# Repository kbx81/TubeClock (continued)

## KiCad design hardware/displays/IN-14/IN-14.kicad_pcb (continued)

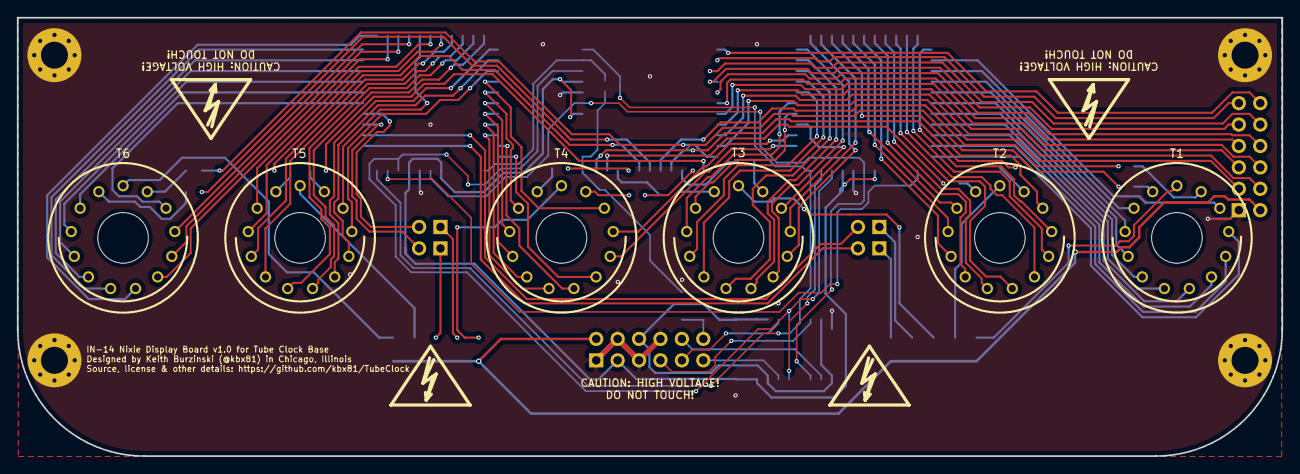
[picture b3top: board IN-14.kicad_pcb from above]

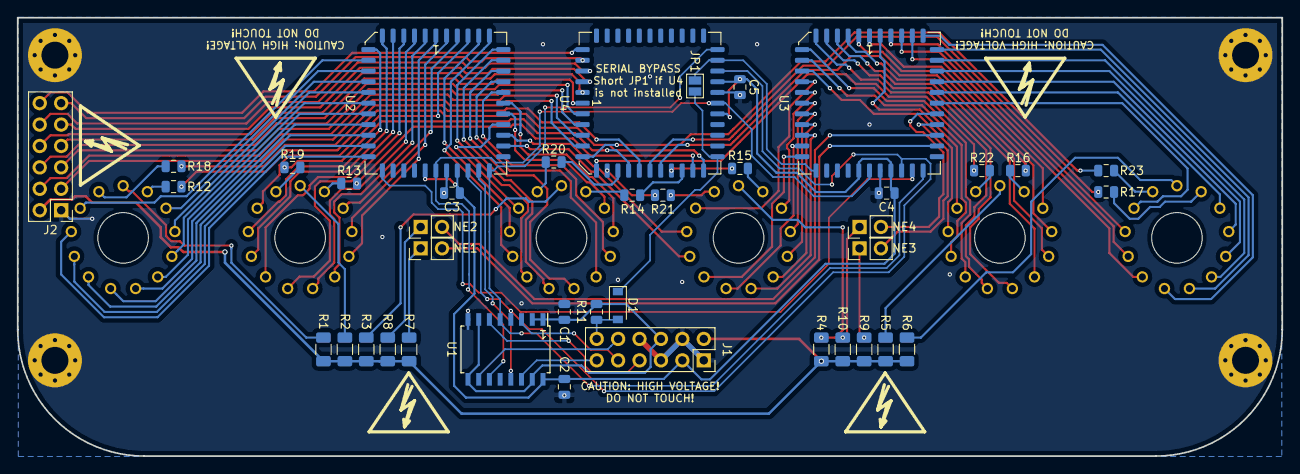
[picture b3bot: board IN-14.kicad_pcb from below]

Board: 2 copper layers, 150.0 x 52.0 mm, 50 parts (40 on the bottom side), 124 nets.

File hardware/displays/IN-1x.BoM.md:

# Nixie Tube Display Board Bill of Materials (BoM)

## Parts

|Reference                                           |Quantity|Value                    |Footprint                                                 |
|----------------------------------------------------|--------|-------------------------|----------------------------------------------------------|
|C2 C1 C3 C4 C5                                      |5       |100 nF, 16 V             |Capacitor_SMD:C_0805_2012Metric                           |
|D1                                                  |1       |1N4148                   |Diode_SMD:D_SOD-123                                       |
|J1                                                  |1       |Conn_02x06_Odd_Even      |Connector_PinSocket_2.54mm:PinSocket_2x06_P2.54mm_Vertical|
|J2                                                  |1       |Conn_02x06_Odd_Even      |Connector_PinHeader_2.54mm:PinHeader_2x06_P2.54mm_Vertical|
|NE4 NE3 NE1 NE2                                     |4       |Lamp_Neon                |Connector_PinHeader_2.54mm:PinHeader_1x02_P2.54mm_Vertical|
|R10 R9 R8 R7                                        |4       |470K                     |Resistor_SMD:R_1206_3216Metric                            |
|R11 R12 R13 R14 R15 R16 R17 R18 R19 R20 R21 R22 R23 |13      |10K                      |Resistor_SMD:R_0805_2012Metric                            |
|R6 R3 R5 R4 R2 R1                                   |6       |10K (2K2 for IN-18) .25 W|Resistor_SMD:R_1206_3216Metric                            |
|T1 T2 T3 T4 T5 T6                                   |6       |IN-1x_Nixie_Tube         |TubeClock:Nixie_IN-1x                                     |
|U1                                                  |1       |CD40109B                 |Package_SO:SOIC-16W_5.3x10.2mm_P1.27mm                    |
|U2 U3 U4*                                           |3       |HV5622                   |Package_LCC:PLCC-44_16.6x16.6mm_P1.27mm                   |

## Additional parts you may need

For IN-12 and IN-18 boards, machine pin sockets are highly recommended -- **do not** solder the tubes into the boards! `Mill-Max` part number `0327-0-15-01-34-27-10-0` is a perfect fit for these tubes!

For the seperator/colon indicator lamps (NE1 through NE4), any "A1B" neon indicator lamp should suffice. I used `VCC` part number `A1B`. Some `INS-1` tubes should also work well, particularly on the IN-12 boards.

## IMPORTANT!

**Pay extra super close attention to the polarity of D1!** Bad things will happen if it is installed backwards. :(

### Notes

For IN-12 and IN-18 tubes, use machine pin sockets suggested above. Since IN-14 and IN-16 tubes have wire leads, they should be soldered directly into the boards.

*U4 is not present on IN-18 display boards. On the other boards, it is not required if you don't care about the lovely decimal points in the smaller tubes. :) **Bridge the solder jumper if U4 is *not* installed** on these boards.

R12 through R23 are additional series resistors for tube decimal points. They are not present on IN-18 boards and are otherwise not necessary if decimal points will not be used.

## Are you shopping?

I've created an [Octopart](https://www.octopart.com) BoM [here](https://octopart.com/bom-tool/LsrgprMy)!

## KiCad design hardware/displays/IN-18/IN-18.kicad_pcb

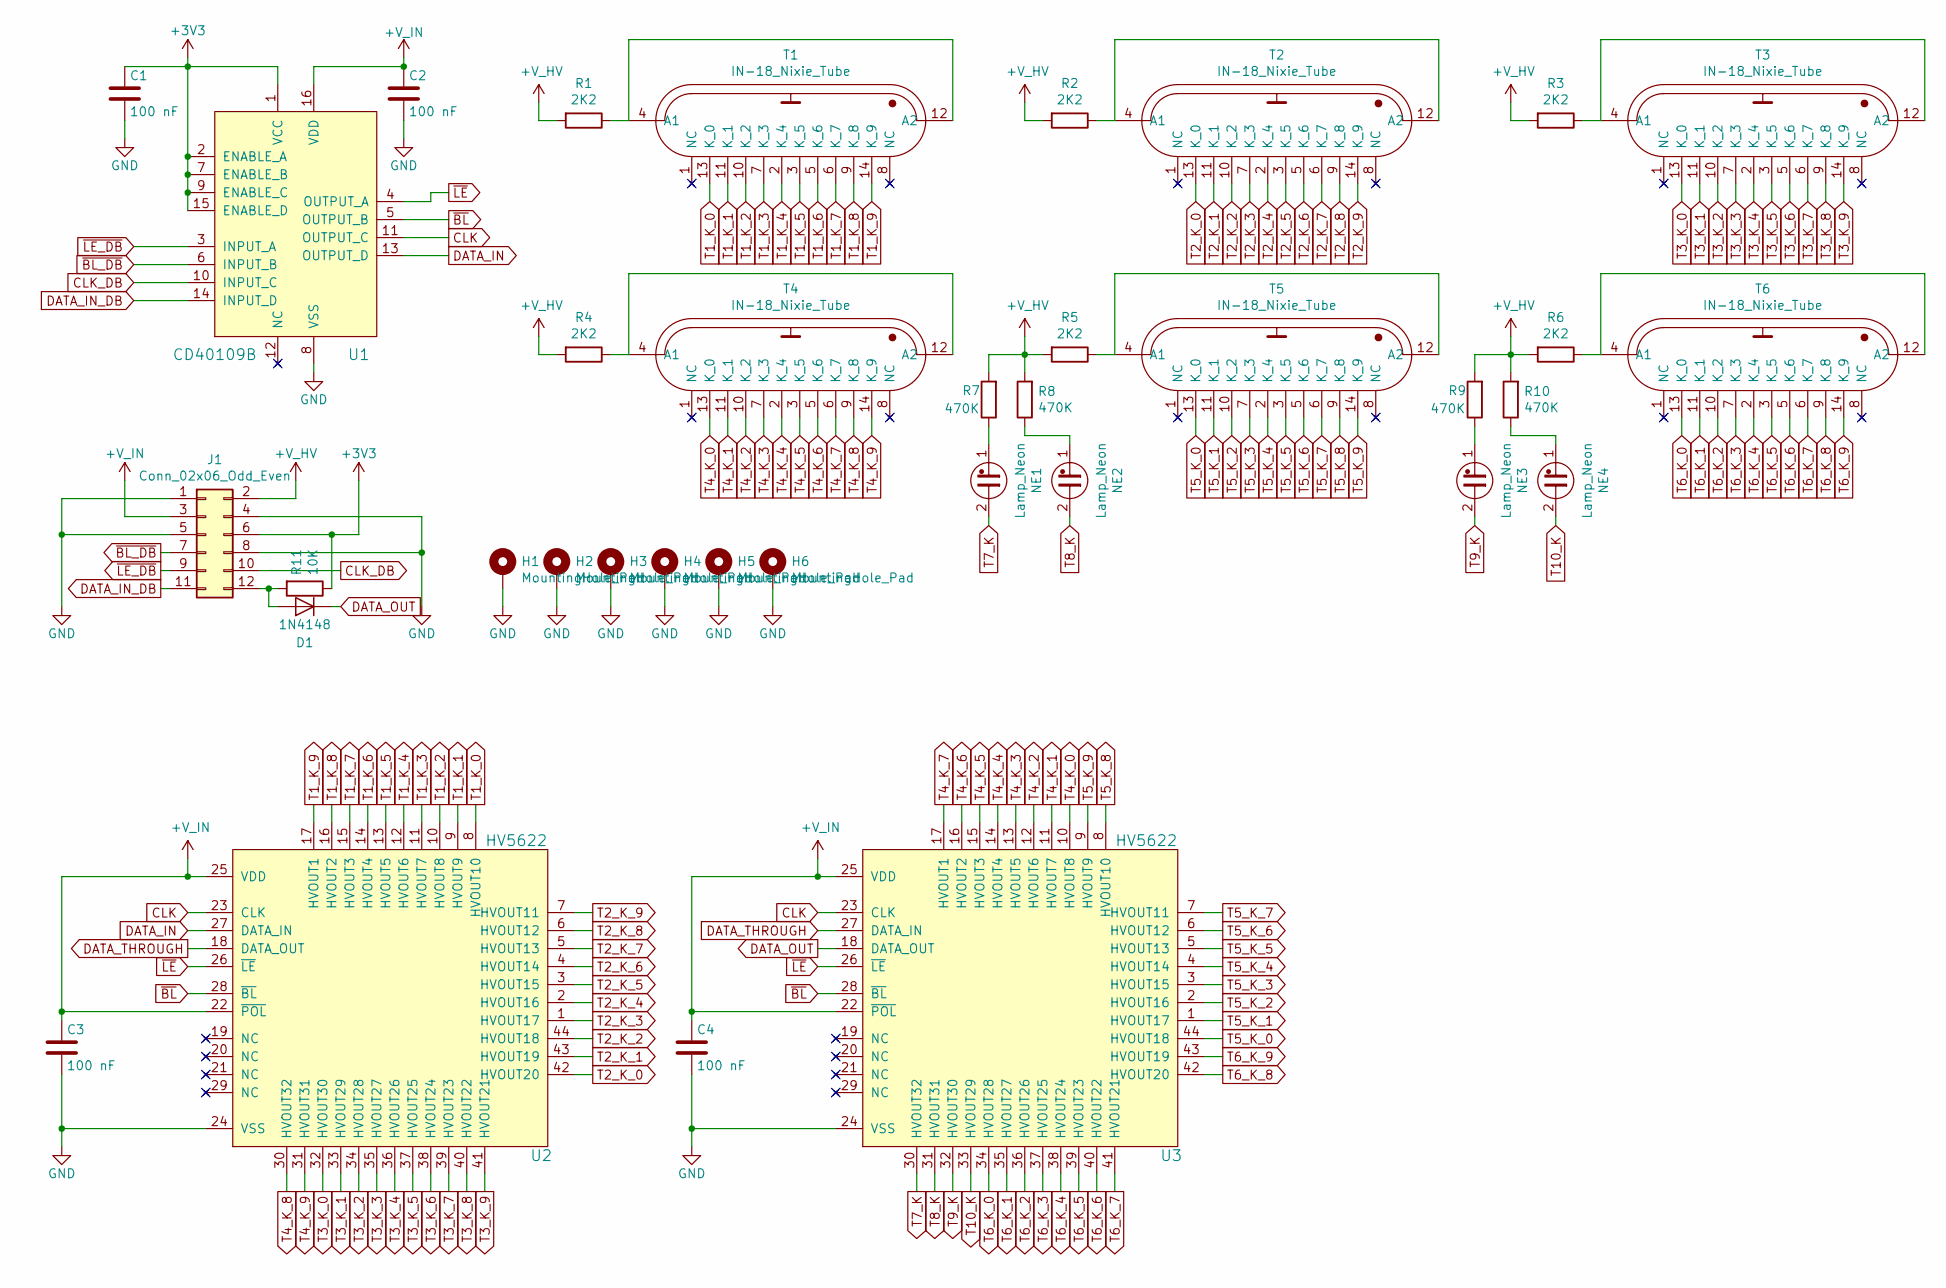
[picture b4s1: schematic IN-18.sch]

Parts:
C1, C2, C3, C4: 100 nF; C_0805_2012Metric
D1: 1N4148; D_SOD-123
H1, H2, H3, H4, H5, H6: MountingHole_Pad; MountingHole_3.2mm_M3_Pad_Via
J1: Conn_02x06_Odd_Even; PinSocket_2x06_P2.54mm_Vertical
NE1, NE2, NE3, NE4: Lamp_Neon; PinSocket_1x02_P2.54mm_Vertical
R1, R2, R3, R4, R5, R6: 2K2; R_1206_3216Metric
R7, R8, R9, R10: 470K; R_1206_3216Metric
R11: 10K; R_0805_2012Metric
T1, T2, T3, T4, T5, T6: IN-18_Nixie_Tube; Nixie_IN-18
U1: CD40109B; SOIC-16W_5.3x10.2mm_P1.27mm
U2, U3: HV5622; PLCC-44_16.6x16.6mm_P1.27mm

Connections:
+3V3: C1.1, J1.6, R11.1, U1.1 (VCC), U1.2 (ENABLE_A), U1.7 (ENABLE_B), U1.9 (ENABLE_C), U1.15 (ENABLE_D)
+V_HV: J1.2, R1.2, R2.2, R3.2, R4.2, R5.2, R6.2, R7.2, R8.2, R9.2, R10.2
+V_IN: C2.1, C3.1, C4.1, J1.3, U1.16 (VDD), U2.22 (~POL~), U2.25 (VDD), U3.22 (~POL~), U3.25 (VDD)
CLK: U1.11 (OUTPUT_C), U2.23 (CLK), U3.23 (CLK)
CLK_DB: J1.10, U1.10 (INPUT_C)
DATA_IN: U1.13 (OUTPUT_D), U2.27 (DATA_IN)
DATA_IN_DB: J1.11, U1.14 (INPUT_D)
DATA_OUT: D1.1 (K), U3.18 (DATA_OUT)
DATA_THROUGH: U2.18 (DATA_OUT), U3.27 (DATA_IN)
GND: C1.2, C2.2, C3.2, C4.2, H1.1, H2.1, H3.1, H4.1, H5.1, H6.1, J1.1, J1.4, J1.5, J1.8, U1.8 (VSS), U2.24 (VSS), U3.24 (VSS)
unnamed: D1.2 (A), J1.12, R11.2
unnamed: NE1.1, R7.1
unnamed: NE2.1, R8.1
unnamed: NE3.1, R9.1
unnamed: NE4.1, R10.1
unnamed: R1.1, T1.4 (A1), T1.12 (A2)
unnamed: R2.1, T2.4 (A1), T2.12 (A2)
unnamed: R3.1, T3.4 (A1), T3.12 (A2)
unnamed: R4.1, T4.4 (A1), T4.12 (A2)
unnamed: R5.1, T5.4 (A1), T5.12 (A2)
unnamed: R6.1, T6.4 (A1), T6.12 (A2)
T1_K_0: T1.13 (K_0), U2.8 (HVOUT10)
T1_K_1: T1.11 (K_1), U2.9 (HVOUT9)
T1_K_2: T1.10 (K_2), U2.10 (HVOUT8)
T1_K_3: T1.7 (K_3), U2.11 (HVOUT7)
T1_K_4: T1.2 (K_4), U2.12 (HVOUT6)
T1_K_5: T1.3 (K_5), U2.13 (HVOUT5)
T1_K_6: T1.5 (K_6), U2.14 (HVOUT4)
T1_K_7: T1.6 (K_7), U2.15 (HVOUT3)
T1_K_8: T1.9 (K_8), U2.16 (HVOUT2)
T1_K_9: T1.14 (K_9), U2.17 (HVOUT1)
T2_K_0: T2.13 (K_0), U2.42 (HVOUT20)
T2_K_1: T2.11 (K_1), U2.43 (HVOUT19)
T2_K_2: T2.10 (K_2), U2.44 (HVOUT18)
T2_K_3: T2.7 (K_3), U2.1 (HVOUT17)
T2_K_4: T2.2 (K_4), U2.2 (HVOUT16)
T2_K_5: T2.3 (K_5), U2.3 (HVOUT15)
T2_K_6: T2.5 (K_6), U2.4 (HVOUT14)
T2_K_7: T2.6 (K_7), U2.5 (HVOUT13)
T2_K_8: T2.9 (K_8), U2.6 (HVOUT12)
T2_K_9: T2.14 (K_9), U2.7 (HVOUT11)
T3_K_0: T3.13 (K_0), U2.32 (HVOUT30)
T3_K_1: T3.11 (K_1), U2.33 (HVOUT29)
T3_K_2: T3.10 (K_2), U2.34 (HVOUT28)
T3_K_3: T3.7 (K_3), U2.35 (HVOUT27)
T3_K_4: T3.2 (K_4), U2.36 (HVOUT26)
T3_K_5: T3.3 (K_5), U2.37 (HVOUT25)
T3_K_6: T3.5 (K_6), U2.38 (HVOUT24)
T3_K_7: T3.6 (K_7), U2.39 (HVOUT23)
T3_K_8: T3.9 (K_8), U2.40 (HVOUT22)
T3_K_9: T3.14 (K_9), U2.41 (HVOUT21)
T4_K_0: T4.13 (K_0), U3.10 (HVOUT8)
T4_K_1: T4.11 (K_1), U3.11 (HVOUT7)
T4_K_2: T4.10 (K_2), U3.12 (HVOUT6)
T4_K_3: T4.7 (K_3), U3.13 (HVOUT5)
T4_K_4: T4.2 (K_4), U3.14 (HVOUT4)
T4_K_5: T4.3 (K_5), U3.15 (HVOUT3)
T4_K_6: T4.5 (K_6), U3.16 (HVOUT2)
T4_K_7: T4.6 (K_7), U3.17 (HVOUT1)
T4_K_8: T4.9 (K_8), U2.30 (HVOUT32)
T4_K_9: T4.14 (K_9), U2.31 (HVOUT31)
T5_K_0: T5.13 (K_0), U3.44 (HVOUT18)
T5_K_1: T5.11 (K_1), U3.1 (HVOUT17)
T5_K_2: T5.10 (K_2), U3.2 (HVOUT16)
T5_K_3: T5.7 (K_3), U3.3 (HVOUT15)
T5_K_4: T5.2 (K_4), U3.4 (HVOUT14)
T5_K_5: T5.3 (K_5), U3.5 (HVOUT13)
T5_K_6: T5.5 (K_6), U3.6 (HVOUT12)
T5_K_7: T5.6 (K_7), U3.7 (HVOUT11)
T5_K_8: T5.9 (K_8), U3.8 (HVOUT10)
T5_K_9: T5.14 (K_9), U3.9 (HVOUT9)
T6_K_0: T6.13 (K_0), U3.34 (HVOUT28)
T6_K_1: T6.11 (K_1), U3.35 (HVOUT27)
T6_K_2: T6.10 (K_2), U3.36 (HVOUT26)
T6_K_3: T6.7 (K_3), U3.37 (HVOUT25)
T6_K_4: T6.2 (K_4), U3.38 (HVOUT24)
T6_K_5: T6.3 (K_5), U3.39 (HVOUT23)
T6_K_6: T6.5 (K_6), U3.40 (HVOUT22)
T6_K_7: T6.6 (K_7), U3.41 (HVOUT21)
T6_K_8: T6.9 (K_8), U3.42 (HVOUT20)
T6_K_9: T6.14 (K_9), U3.43 (HVOUT19)
T7_K: NE1.2, U3.30 (HVOUT32)
T8_K: NE2.2, U3.31 (HVOUT31)
T9_K: NE3.2, U3.32 (HVOUT30)
T10_K: NE4.2, U3.33 (HVOUT29)
~BL_DB~: J1.7, U1.6 (INPUT_B)
~BL~: U1.5 (OUTPUT_B), U2.28 (~BL~), U3.28 (~BL~)
~LE_DB~: J1.9, U1.3 (INPUT_A)
~LE~: U1.4 (OUTPUT_A), U2.26 (~LE~), U3.26 (~LE~)

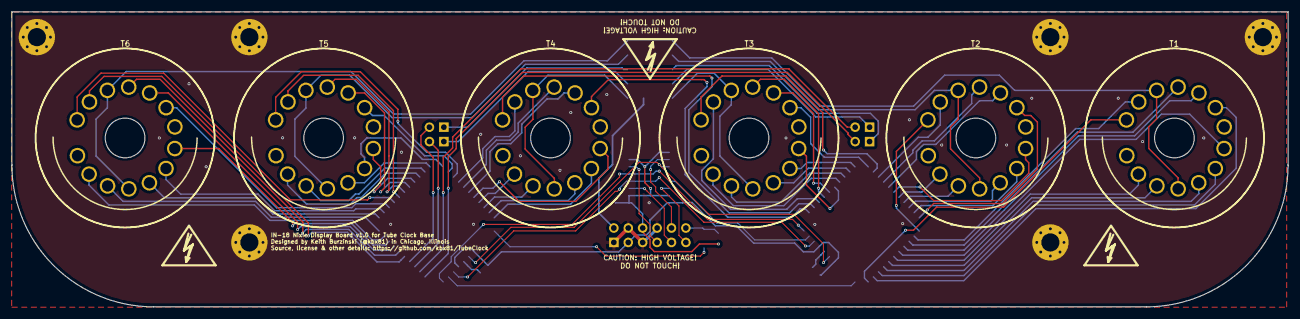
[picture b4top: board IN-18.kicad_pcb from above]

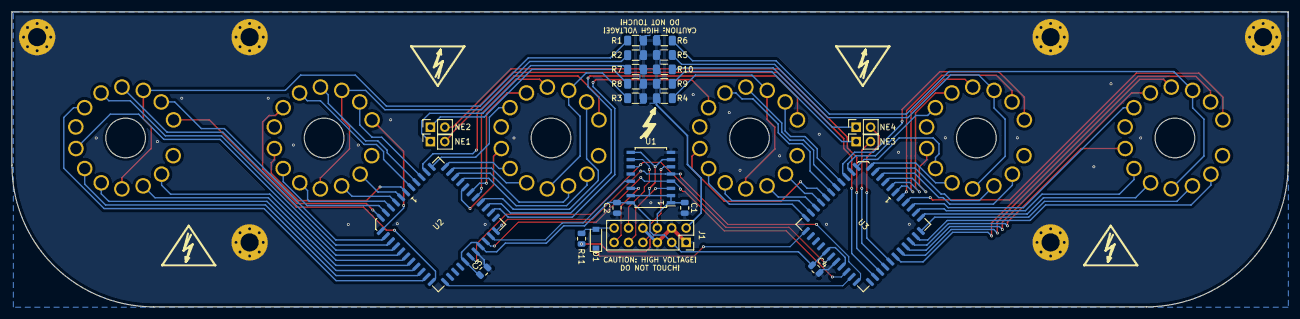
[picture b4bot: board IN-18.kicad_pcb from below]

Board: 2 copper layers, 225.0 x 52.0 mm, 36 parts (24 on the bottom side), 89 nets.

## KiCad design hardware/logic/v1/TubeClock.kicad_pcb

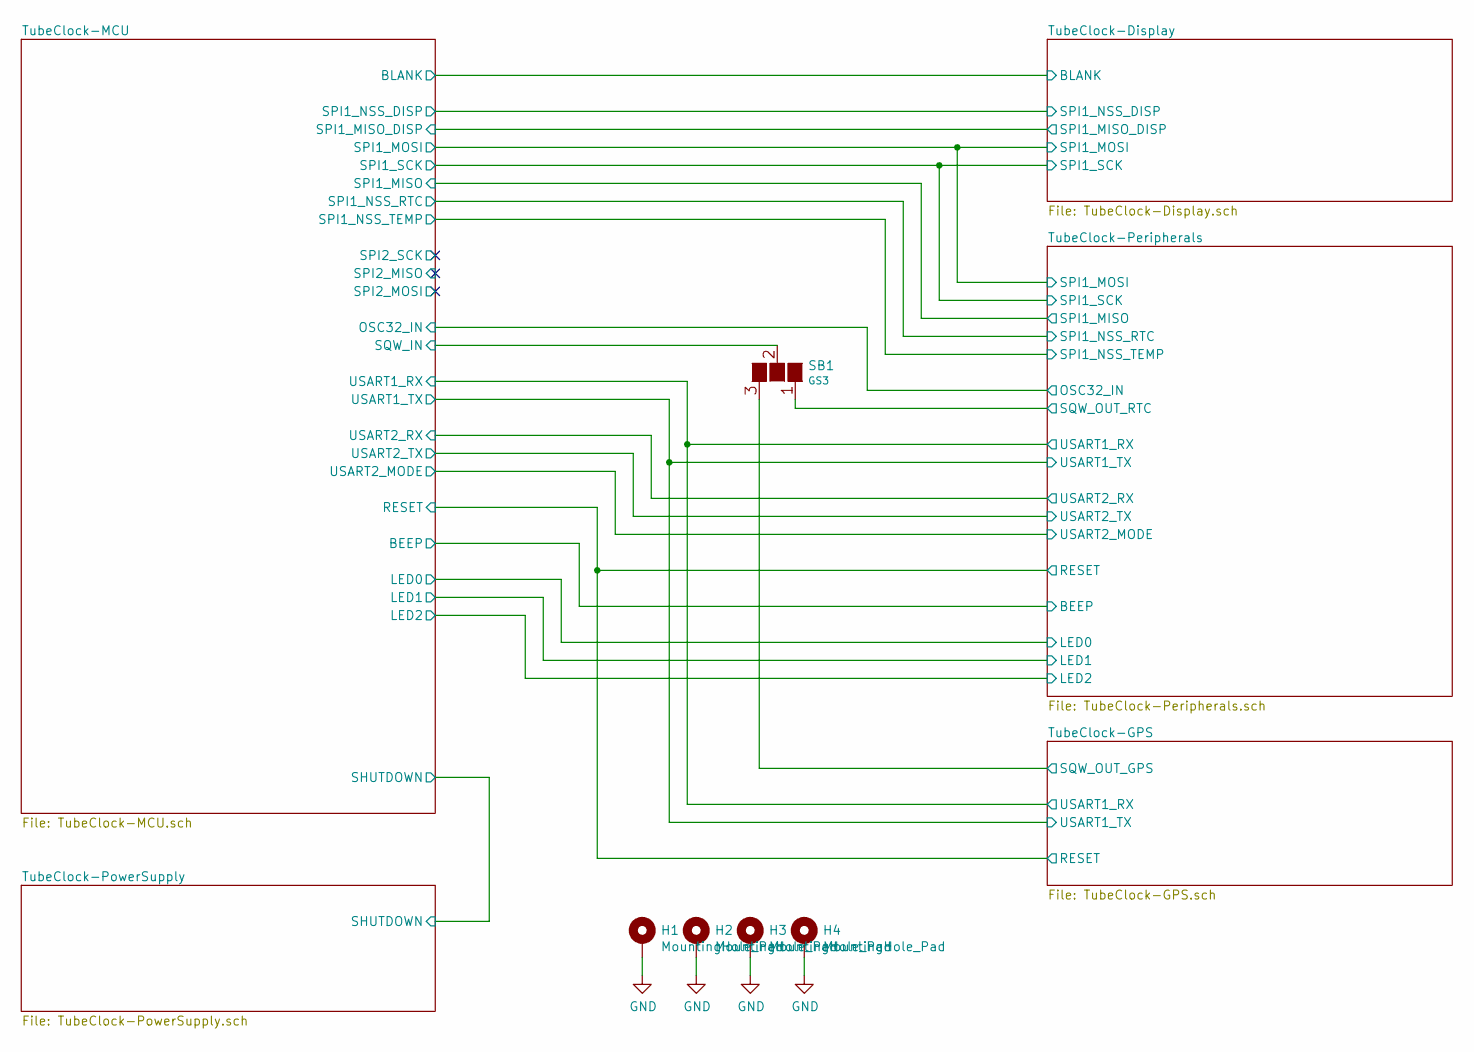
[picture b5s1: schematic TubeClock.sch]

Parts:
H1, H2, H3, H4: MountingHole_Pad; MountingHole_3.2mm_M3_Pad_Via
SB1: GS3; SolderJumper-3_P1.3mm_Open_Pad1.0x1.5mm

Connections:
/TubeClock-GPS/SQW_OUT_GPS: SB1.3 (G3); also elsewhere on the board
/TubeClock-MCU/SQW_IN: SB1.2 (G2); also elsewhere on the board
/TubeClock-Peripherals/SQW_OUT_RTC: SB1.1 (G1); also elsewhere on the board
GND: H1.1, H2.1, H3.1, H4.1; also elsewhere on the board

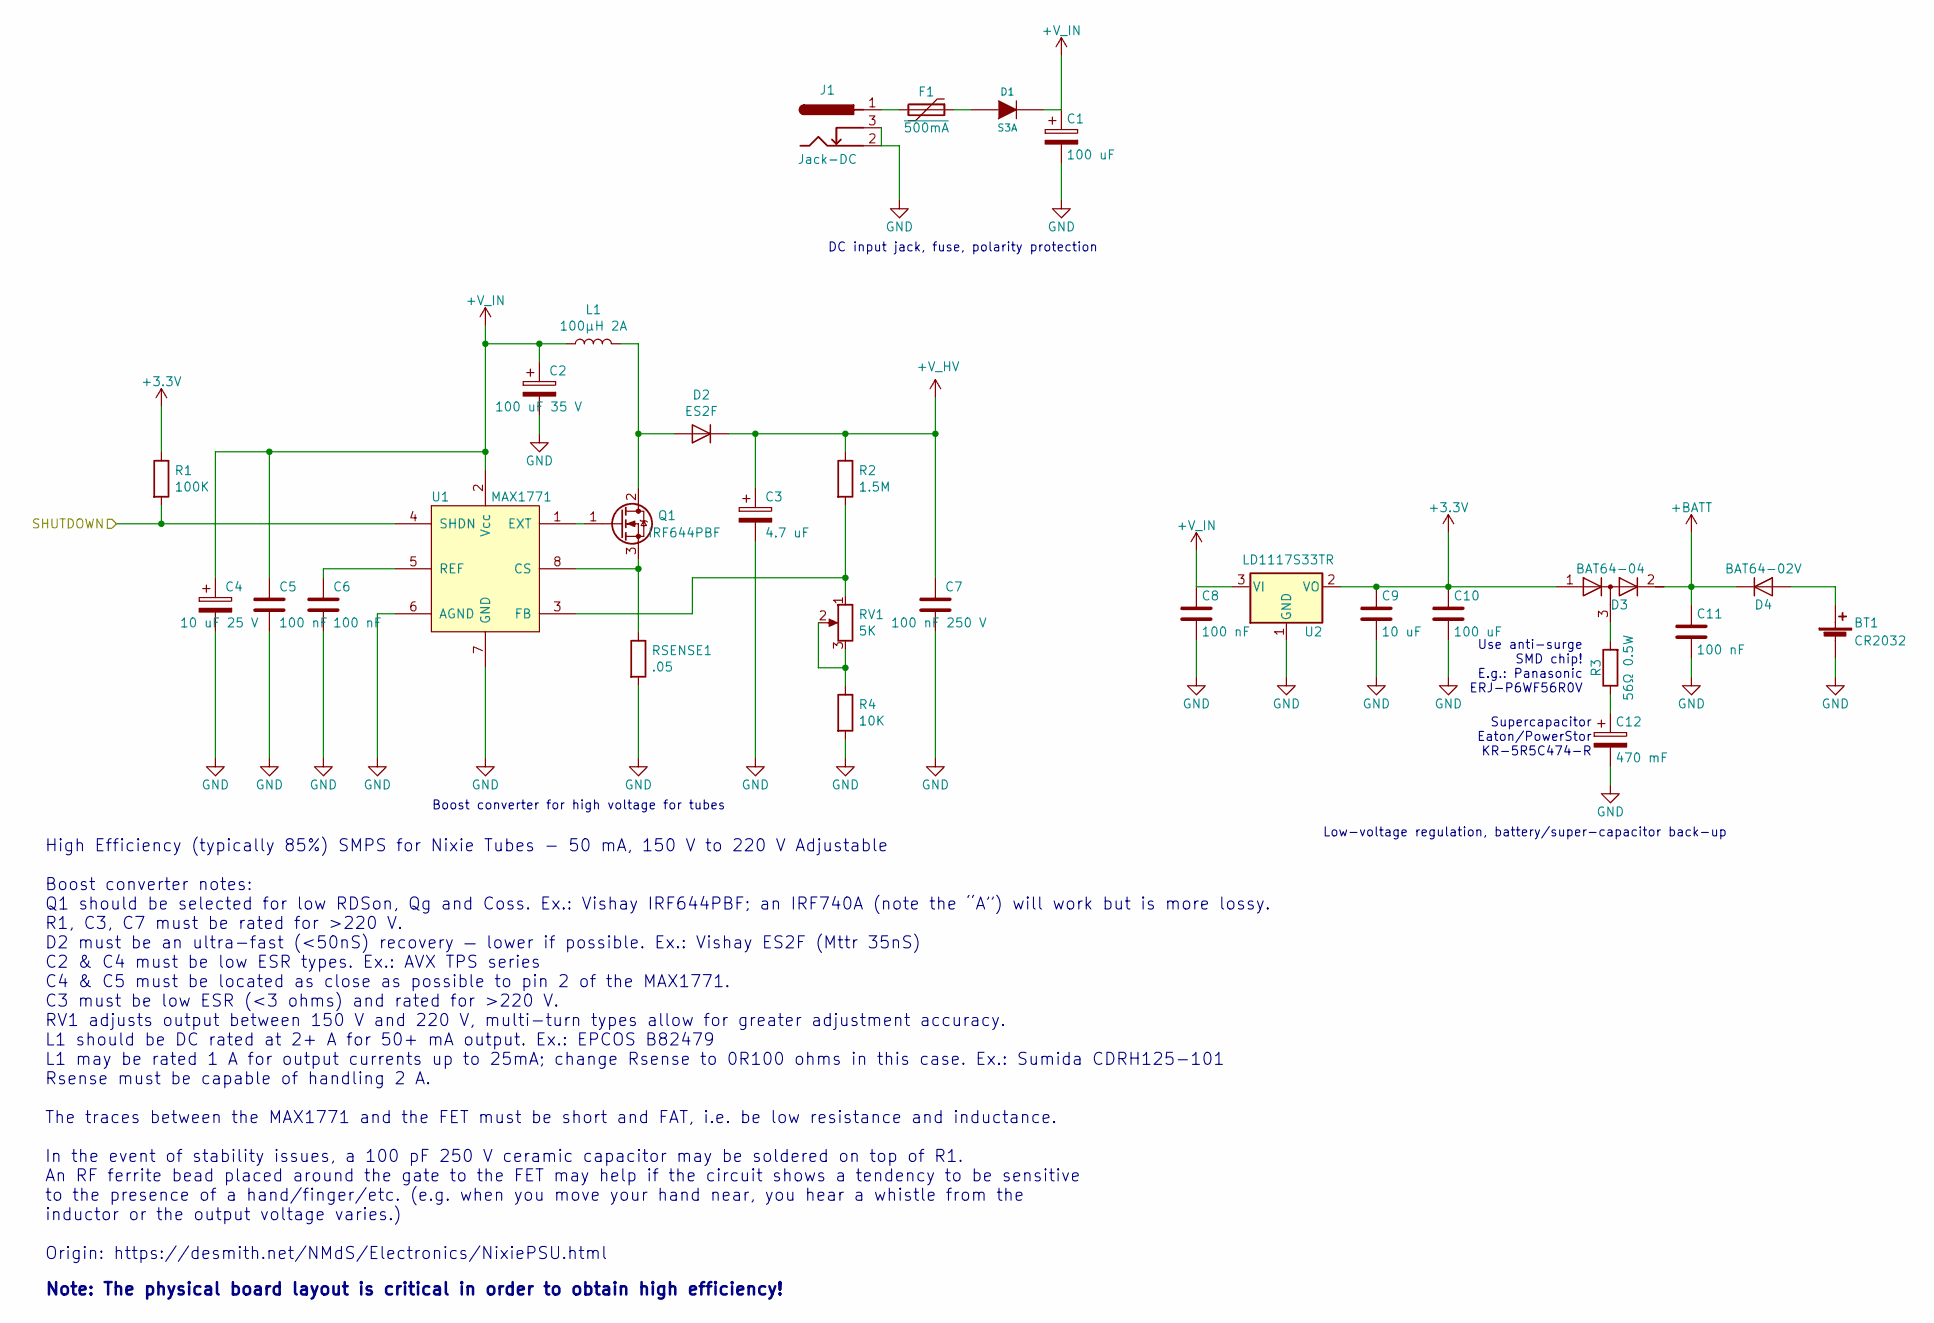
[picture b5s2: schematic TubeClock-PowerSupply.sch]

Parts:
BT1: CR2032; BatteryHolder_Keystone_3034_1x20mm; Part Number 103
C1: 100 uF; CP_Elec_8x10; Part Number 25SVF100M
C2: 100 uF 35 V; CP_EIA-7343-31_Kemet-D
C3: 4.7 uF; CP_Elec_10x10
C4: 10 uF 25 V; CP_EIA-7343-31_Kemet-D
C5, C6, C8, C11: 100 nF; C_0805_2012Metric
C7: 100 nF 250 V; C_2420_HandSoldering
C9: 10 uF; C_0805_2012Metric
C10: 100 uF; CP_Elec_5x5.3
C12: 470 mF; CP_Radial_D13.0mm_P5.00mm_HD1.5mm; Part Number KR-5R5H474-R
D1: S3A; D_SMC; Part Number S3A
D2: ES2F; D_SMB
D3: BAT64-04; SOT-23
D4: BAT64-02V; D_0603_1608Metric
F1: ~500mA; Fuse_2920_7451Metric; Part Number 2920L185DR
J1: Jack-DC; BarrelJack_Horizontal
L1: 100µH 2A; L_EPCOS_B82479A1_Handsoldering
Q1: IRF644PBF; TO-220-3_Horizontal_TabDown
R1: 100K; R_0805_2012Metric
R2: 1.5M; R_2512_6332Metric
R3: 56Ω 0.5W; R_0805_2012Metric
R4: 10K; R_0805_2012Metric
RSENSE1: .05; R_2010_5025Metric
RV1: 5K; Potentiometer_Bourns_3214W_Vertical
U1: MAX1771; SOIC-8_3.9x4.9mm_P1.27mm
U2: LD1117S33TR; TO-252-2; Part Number LD1117ADT33TR

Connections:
+3V3: C9.1, C10.1, D3.1 (A), R1.1, U2.2 (VO); also elsewhere on the board
+BATT: C11.1, D3.2 (K), D4.1 (K); also elsewhere on the board
+V_HV: C3.1, C7.1, D2.1 (K), R2.1; also elsewhere on the board
+V_IN: C1.1, C2.1, C4.1, C5.1, C8.1, D1.2 (K), L1.1, U1.2 (Vcc), U2.3 (VI); also elsewhere on the board
/TubeClock-MCU/SHUTDOWN: R1.2, U1.4 (SHDN); also elsewhere on the board
GND: BT1.2 (-), C1.2, C2.2, C3.2, C4.2, C5.2, C6.2, C7.2, C8.2, C9.2, C10.2, C11.2, C12.2, J1.2, J1.3, R4.2, RSENSE1.2, U1.6 (AGND), U1.7 (GND), U2.1 (GND); also elsewhere on the board
unnamed: BT1.1 (+), D4.2 (A)
unnamed: C6.1, U1.5 (REF)
unnamed: C12.1, R3.1
unnamed: D1.1 (A), F1.1
unnamed: D2.2 (A), L1.2, Q1.2 (D)
unnamed: D3.3 (common), R3.2
unnamed: F1.2, J1.1
unnamed: Q1.1 (G), U1.1 (EXT)
unnamed: Q1.3 (S), RSENSE1.1, U1.8 (CS)
unnamed: R2.2, RV1.1, U1.3 (FB)
unnamed: R4.1, RV1.2, RV1.3

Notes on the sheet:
Supercapacitor Eaton/PowerStor KR-5R5C474-R
Use anti-surge SMD chip! E.g.: Panasonic ERJ-P6WF56R0V
Note: The physical board layout is critical in order to obtain high efficiency!
High Efficiency (typically 85%) SMPS for Nixie Tubes - 50 mA, 150 V to 220 V Adjustable Boost converter notes: Q1 should be selected for low RDSon, Qg and Coss. Ex.: Vishay IRF644PBF; an IRF740A (note the “A”) will work but is more lossy. R1, C3, C7 must be rated for >220 V. D2 must be an ultra-fas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
DC input jack, fuse, polarity protection
Low-voltage regulation, battery/super-capacitor back-up
Boost converter for high voltage for tubes

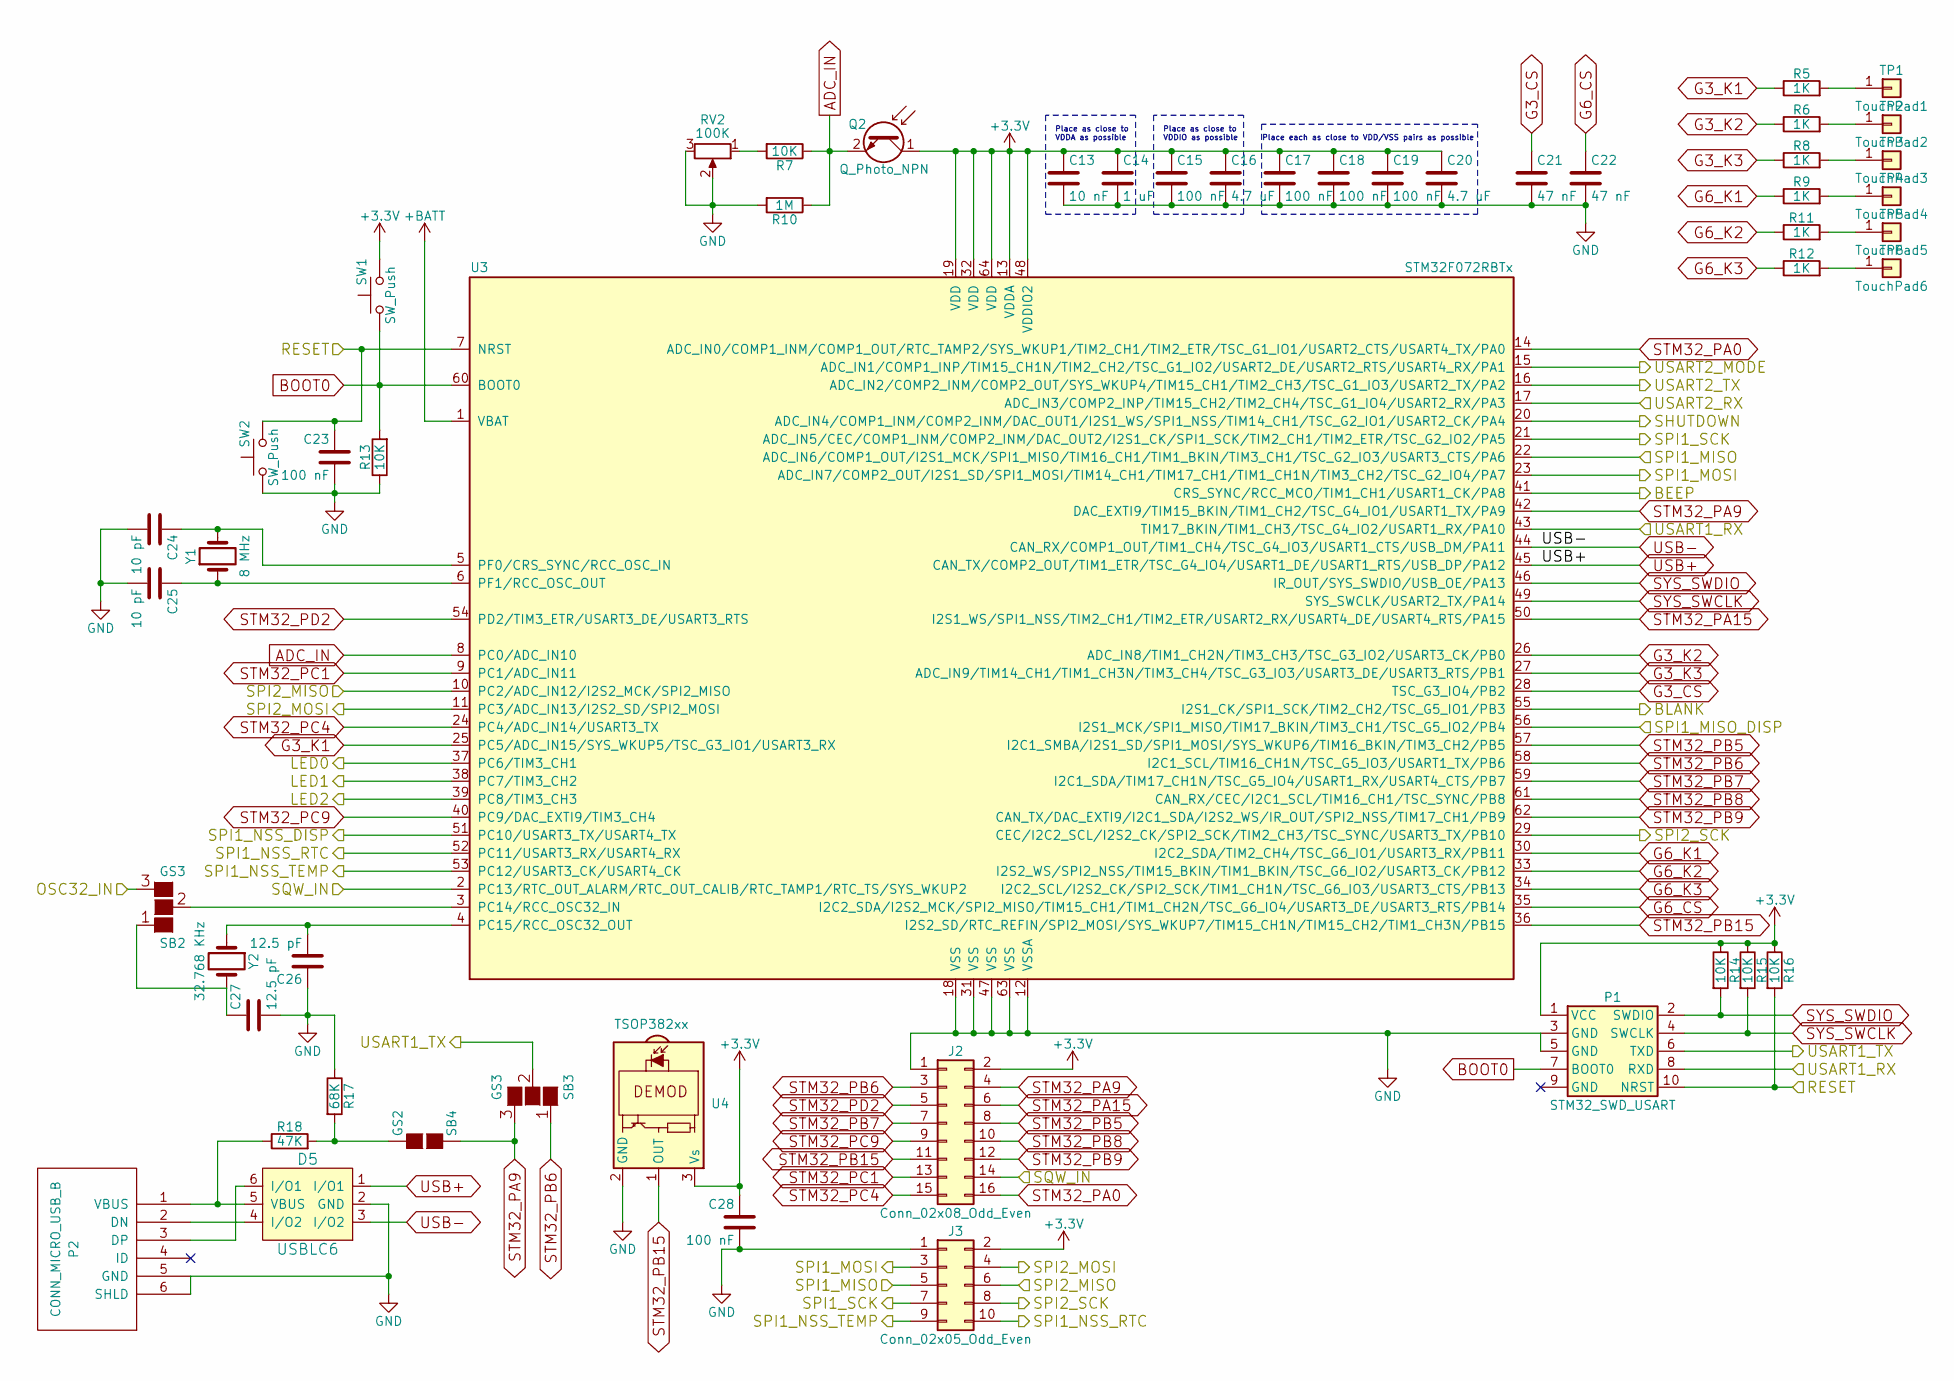
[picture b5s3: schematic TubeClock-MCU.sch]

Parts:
C13: 10 nF; C_0805_2012Metric
C14: 1 uF; C_0805_2012Metric
C15, C17, C18, C19, C23, C28: 100 nF; C_0805_2012Metric
C16, C20: 4.7 uF; C_0805_2012Metric
C21, C22: 47 nF; C_0805_2012Metric
C24, C25: 10 pF; C_0805_2012Metric
C26, C27: 12.5 pF; C_0805_2012Metric
D5: USBLC6; SOT-23-6
J2: Conn_02x08_Odd_Even; PinHeader_2x08_P2.54mm_Vertical
J3: Conn_02x05_Odd_Even; PinHeader_2x05_P2.54mm_Vertical
P1: STM32_SWD_USART; PinHeader_2x05_P1.27mm_Vertical_SMD; Part Number M50-3600542R
P2: CONN_MICRO_USB_B; USB_Micro-B_Molex-105017-0001
Q2: Q_Photo_NPN; LED_D5.0mm_Clear; Part Number TEPT5600
R5, R6, R8, R9, R11, R12: 1K; R_0805_2012Metric
R7, R13, R14, R15, R16: 10K; R_0805_2012Metric
R10: 1M; R_0805_2012Metric
R17: 68K; R_0805_2012Metric
R18: 47K; R_0805_2012Metric
RV2: 100K; Potentiometer_Vishay_TS53YJ_Vertical; Part Number TC33X-2-104E
SB2, SB3: GS3; SolderJumper-3_P1.3mm_Open_Pad1.0x1.5mm
SB4: GS2; SolderJumper-2_P1.3mm_Open_Pad1.0x1.5mm
SW1, SW2: SW_Push; SW_Push_1P1T_NO_CK_KMR2; Part Number KMR221G LFS
TP1: TouchPad1
TP2: TouchPad2; TouchPad1
TP3: TouchPad3; TouchPad1
TP4: TouchPad4; TouchPad1
TP5: TouchPad5; TouchPad1
TP6: TouchPad6; TouchPad1
U3: STM32F072RBTx; LQFP-64_10x10mm_P0.5mm
U4: TSOP382xx; Vishay_MINICAST-3Pin
Y1: 8 MHz; Crystal_SMD_5032-4Pin_5.0x3.2mm; Part Number ABM3B-8.000MHZ-10-1UT
Y2: 32.768 KHz; Crystal_SMD_3215-2Pin_3.2x1.5mm; Part Number ECX-.327-CDX-1293

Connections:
+3V3: C13.1, C14.1, C15.1, C16.1, C17.1, C18.1, C19.1, C20.1, C28.1, J2.2, J3.2, P1.1 (VCC), Q2.1 (C), R14.1, R15.1, R16.1, SW1.2, U3.13 (VDDA), U3.19 (VDD), U3.32 (VDD), U3.48 (VDDIO2), U3.64 (VDD), U4.3 (Vs); also elsewhere on the board
+BATT: U3.1 (VBAT); also elsewhere on the board
/TubeClock-Display/BLANK: U3.55 (I2S1_CK/SPI1_SCK/TIM2_CH2/TSC_G5_IO1/PB3); also elsewhere on the board
/TubeClock-Display/SPI1_MISO_DISP: U3.56 (I2S1_MCK/SPI1_MISO/TIM17_BKIN/TIM3_CH1/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); also elsewhere on the board
/TubeClock-Display/SPI1_MOSI: J3.3, U3.23 (ADC_IN7/COMP2_OUT/I2S1_SD/SPI1_MOSI/TIM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); also elsewhere on the board
/TubeClock-Display/SPI1_NSS_DISP: U3.51 (PC10/USART3_TX/USART4_TX); also elsewhere on the board
/TubeClock-Display/SPI1_SCK: J3.7, U3.21 (ADC_IN5/CEC/COMP1_INM/COMP2_INM/DAC_OUT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); also elsewhere on the board
/TubeClock-GPS/RESET: C23.1, P1.10 (NRST), R16.2, SW2.2, U3.7 (NRST); also elsewhere on the board
/TubeClock-GPS/USART1_RX: P1.8 (RXD), U3.43 (TIM17_BKIN/TIM1_CH3/TSC_G4_IO2/USART1_R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); also elsewhere on the board
/TubeClock-GPS/USART1_TX: P1.6 (TXD), SB3.2 (G2); also elsewhere on the board
/TubeClock-MCU/BEEP: U3.41 (CRS_SYNC/RCC_MCO/TIM1_CH1/USART1_CK/PA8); also elsewhere on the board
/TubeClock-MCU/LED0: U3.37 (PC6/TIM3_CH1); also elsewhere on the board
/TubeClock-MCU/LED1: U3.38 (PC7/TIM3_CH2); also elsewhere on the board
/TubeClock-MCU/LED2: U3.39 (PC8/TIM3_CH3); also elsewhere on the board
/TubeClock-MCU/OSC32_IN: SB2.3 (G3); also elsewhere on the board
/TubeClock-MCU/SHUTDOWN: U3.20 (ADC_IN4/COMP1_INM/COMP2_INM/DAC_OUT1/I2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); also elsewhere on the board
/TubeClock-MCU/SPI1_MISO: J3.5, U3.22 (ADC_IN6/COMP1_OUT/I2S1_MCK/SPI1_MISO/TI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); also elsewhere on the board
/TubeClock-MCU/SPI1_NSS_RTC: J3.10, U3.52 (PC11/USART3_RX/USART4_RX); also elsewhere on the board
/TubeClock-MCU/SPI1_NSS_TEMP: J3.9, U3.53 (PC12/USART3_CK/USART4_CK); also elsewhere on the board
/TubeClock-MCU/SPI2_MISO: J3.6, U3.10 (PC2/ADC_IN12/I2S2_MCK/SPI2_MISO)
/TubeClock-MCU/SPI2_MOSI: J3.4, U3.11 (PC3/ADC_IN13/I2S2_SD/SPI2_MOSI)
/TubeClock-MCU/SPI2_SCK: J3.8, U3.29 (CEC/I2C2_SCL/I2S2_CK/SPI2_SCK/TIM2_CH3/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)
/TubeClock-MCU/SQW_IN: J2.14, U3.2 (PC13/RTC_OUT_ALARM/RTC_OUT_CALIB/RTC_TA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); also elsewhere on the board
/TubeClock-MCU/USART2_MODE: U3.15 (ADC_IN1/COMP1_INP/TIM15_CH1N/TIM2_CH2/T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); also elsewhere on the board
/TubeClock-MCU/USART2_RX: U3.17 (ADC_IN3/COMP2_INP/TIM15_CH2/TIM2_CH4/TS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); also elsewhere on the board
/TubeClock-MCU/USART2_TX: U3.16 (ADC_IN2/COMP2_INM/COMP2_OUT/SYS_WKUP4/T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); also elsewhere on the board
ADC_IN: Q2.2 (E), R7.1, R10.1, U3.8 (PC0/ADC_IN10)
BOOT0: P1.7 (BOOT0), R13.2, SW1.1, U3.60 (BOOT0)
G3_CS: C21.1, U3.28 (TSC_G3_IO4/PB2)
G3_K1: R5.1, U3.25 (PC5/ADC_IN15/SYS_WKUP5/TSC_G3_IO1/USART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)
G3_K2: R6.1, U3.26 (ADC_IN8/TIM1_CH2N/TIM3_CH3/TSC_G3_IO2/U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)
G3_K3: R8.1, U3.27 (ADC_IN9/TIM14_CH1/TIM1_CH3N/TIM3_CH4/TS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)
G6_CS: C22.1, U3.35 (I2C2_SDA/I2S2_MCK/SPI2_MISO/TIM15_CH1/T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)
G6_K1: R9.1, U3.30 (I2C2_SDA/TIM2_CH4/TSC_G6_IO1/USART3_RX/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)
G6_K2: R11.1, U3.33 (I2S2_WS/SPI2_NSS/TIM15_BKIN/TIM1_BKIN/T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)
G6_K3: R12.1, U3.34 (I2C2_SCL/I2S2_CK/SPI2_SCK/TIM1_CH1N/TSC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)
GND: C13.2, C14.2, C15.2, C16.2, C17.2, C18.2, C19.2, C20.2, C21.2, C22.2, C23.2, C24.2, C25.2, C26.1, C27.2, C28.2, D5.2 (GND), J2.1, J3.1, P1.3 (GND), P1.5 (GND), P2.5 (GND), P2.6 (SHLD), R10.2, R13.1, R17.1, RV2.2, RV2.3, SW2.1, U3.12 (VSSA), U3.18 (VSS), U3.31 (VSS), U3.47 (VSS), U3.63 (VSS), U4.2 (GND); also elsewhere on the board
unnamed: C24.1, U3.5 (PF0/CRS_SYNC/RCC_OSC_IN), Y1.2
unnamed: C25.1, U3.6 (PF1/RCC_OSC_OUT), Y1.1
unnamed: C26.2, U3.4 (PC15/RCC_OSC32_OUT), Y2.1
unnamed: C27.1, SB2.1 (G1), Y2.2
unnamed: D5.4 (I/O2), P2.2 (DN)
unnamed: D5.5 (VBUS), P2.1 (VBUS), R18.1
unnamed: D5.6 (I/O1), P2.3 (DP)
unnamed: R5.2, TP1.1
unnamed: R6.2, TP2.1
unnamed: R7.2, RV2.1
unnamed: R8.2, TP3.1
unnamed: R9.2, TP4.1
unnamed: R11.2, TP5.1
unnamed: R12.2, TP6.1
unnamed: R17.2, R18.2, SB4.2 (G2)
unnamed: SB2.2 (G2), U3.3 (PC14/RCC_OSC32_IN)
STM32_PA0: J2.16, U3.14 (ADC_IN0/COMP1_INM/COMP1_OUT/RTC_TAMP2/S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)
STM32_PA9: J2.4, SB3.3 (G3), SB4.1 (G1), U3.42 (DAC_EXTI9/TIM15_BKIN/TIM1_CH2/TSC_G4_IO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)
STM32_PA15: J2.6, U3.50 (I2S1_WS/SPI1_NSS/TIM2_CH1/TIM2_ETR/USAR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)
STM32_PB5: J2.8, U3.57 (I2C1_SMBA/I2S1_SD/SPI1_MOSI/SYS_WKUP6/T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)
STM32_PB6: J2.3, SB3.1 (G1), U3.58 (I2C1_SCL/TIM16_CH1N/TSC_G5_IO3/USART1_T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)
STM32_PB7: J2.7, U3.59 (I2C1_SDA/TIM17_CH1N/TSC_G5_IO4/USART1_R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)
STM32_PB8: J2.10, U3.61 (CAN_RX/CEC/I2C1_SCL/TIM16_CH1/TSC_SYNC/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)
STM32_PB9: J2.12, U3.62 (CAN_TX/DAC_EXTI9/I2C1_SDA/I2S2_WS/IR_OU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)
STM32_PB15: J2.11, U3.36 (I2S2_SD/RTC_REFIN/SPI2_MOSI/SYS_WKUP7/T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), U4.1 (OUT)
STM32_PC1: J2.13, U3.9 (PC1/ADC_IN11)
STM32_PC4: J2.15, U3.24 (PC4/ADC_IN14/USART3_TX)
STM32_PC9: J2.9, U3.40 (PC9/DAC_EXTI9/TIM3_CH4)
STM32_PD2: J2.5, U3.54 (PD2/TIM3_ETR/USART3_DE/USART3_RTS)
SYS_SWCLK: P1.4 (SWCLK), R15.2, U3.49 (SYS_SWCLK/USART2_TX/PA14)
SYS_SWDIO: P1.2 (SWDIO), R14.2, U3.46 (IR_OUT/SYS_SWDIO/USB_OE/PA13)
USB+: D5.1 (I/O1), U3.45 (CAN_TX/COMP2_OUT/TIM1_ETR/TSC_G4_IO4/US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)
USB-: D5.3 (I/O2), U3.44 (CAN_RX/COMP1_OUT/TIM1_CH4/TSC_G4_IO3/US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)

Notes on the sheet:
Place as close to VDDA as possible
Place as close to VDDIO as possible
Place each as close to VDD/VSS pairs as possible

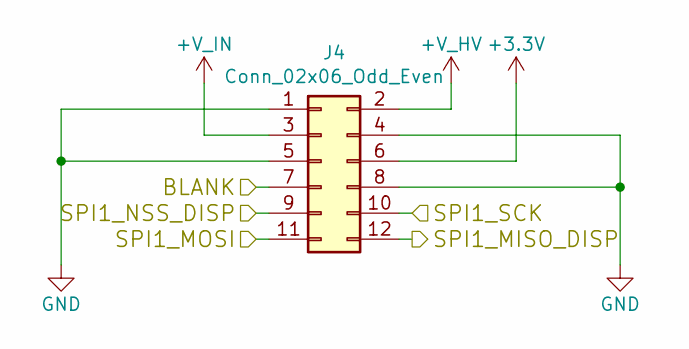
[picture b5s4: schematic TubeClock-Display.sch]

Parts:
J4: Conn_02x06_Odd_Even; PinHeader_2x06_P2.54mm_Vertical

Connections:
+3V3: J4.6; also elsewhere on the board
+V_HV: J4.2; also elsewhere on the board
+V_IN: J4.3; also elsewhere on the board
/TubeClock-Display/BLANK: J4.7; also elsewhere on the board
/TubeClock-Display/SPI1_MISO_DISP: J4.12; also elsewhere on the board
/TubeClock-Display/SPI1_MOSI: J4.11; also elsewhere on the board
/TubeClock-Display/SPI1_NSS_DISP: J4.9; also elsewhere on the board
/TubeClock-Display/SPI1_SCK: J4.10; also elsewhere on the board
GND: J4.1, J4.4, J4.5, J4.8; also elsewhere on the board
